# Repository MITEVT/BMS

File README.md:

BMS
===

directory structure
-------------------
software:
firmware:
schematics:

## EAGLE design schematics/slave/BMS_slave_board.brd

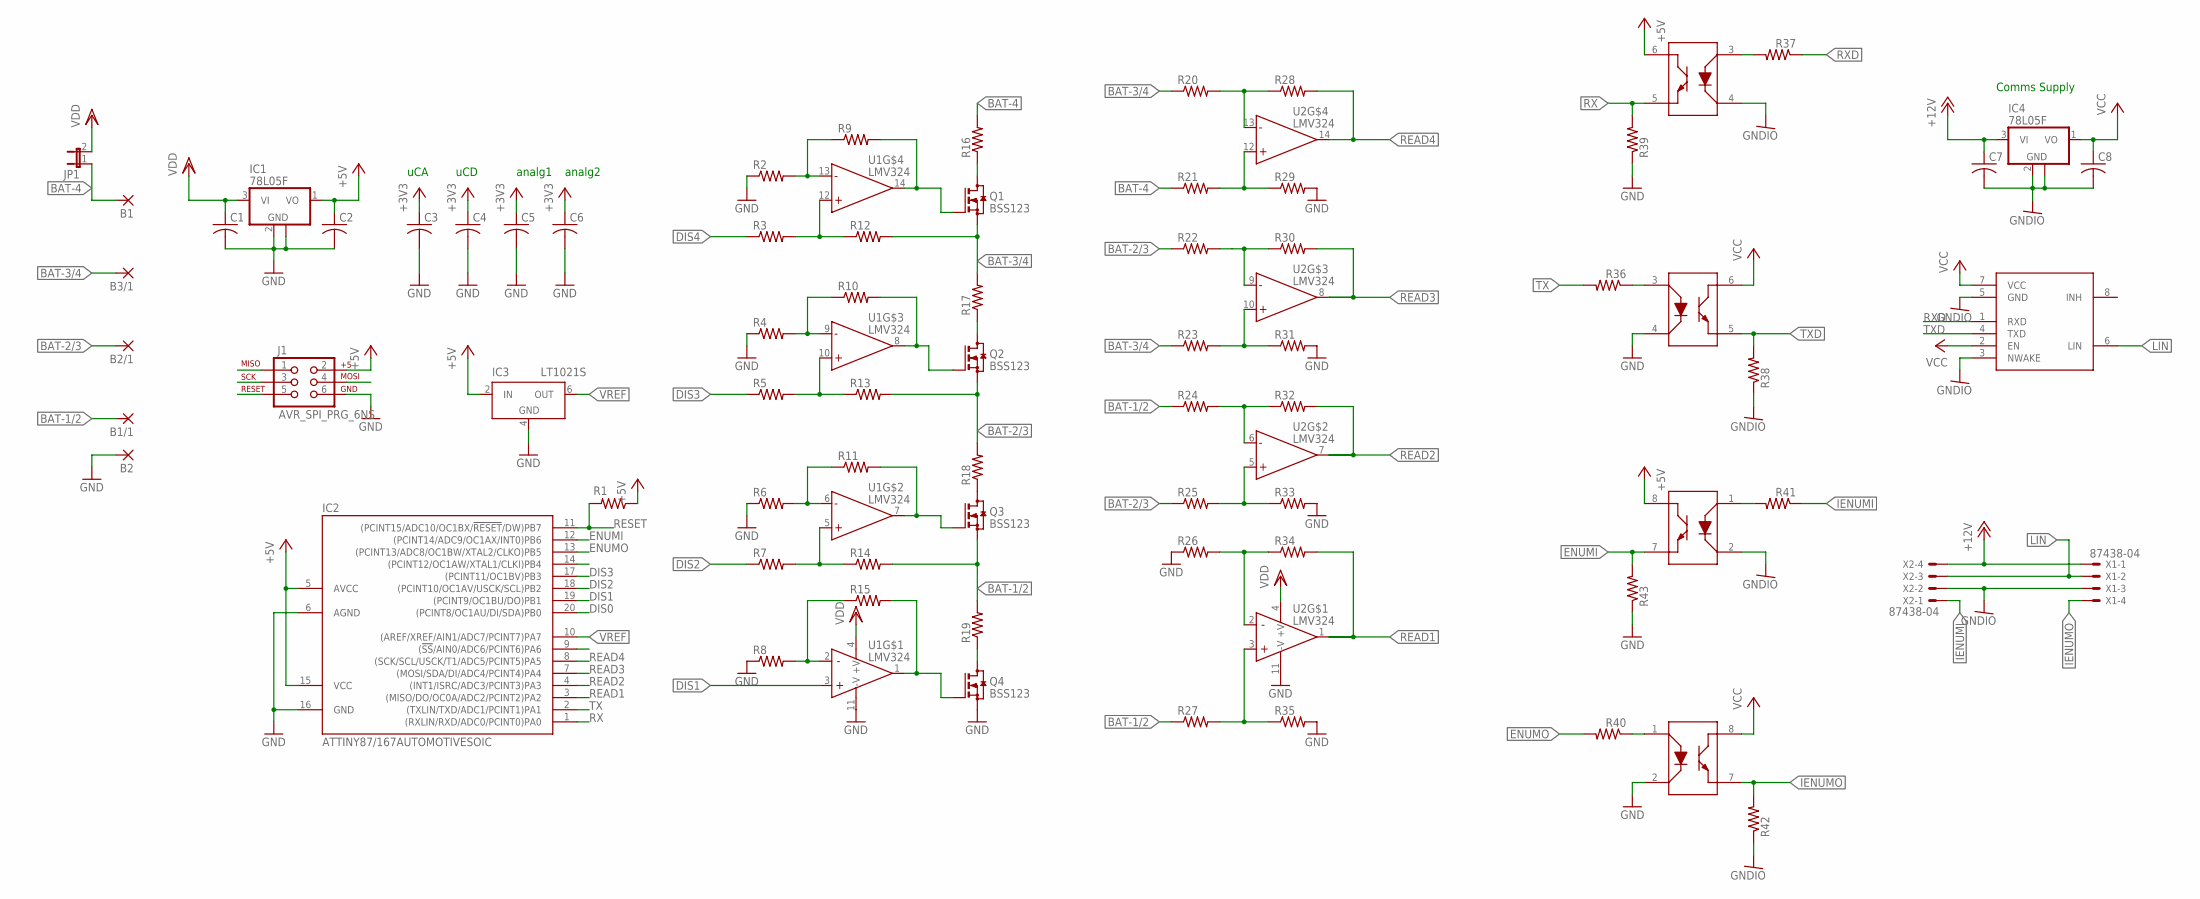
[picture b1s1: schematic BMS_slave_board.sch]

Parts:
B1, B1/1, B2, B2/1, B3/1: 2,15/1,0
C1, C2, C3, C4, C5, C6, C7, C8: C-US025-024X044; C025-024X044
IC1, IC4: 78L05F; SOT89
IC2: ATTINY87/167AUTOMOTIVESOIC; SO20L
IC3: LT1021S; SOIC8
J1: AVR_SPI_PRG_6NS; 2X3-NS
JP1: JP1E; JP1
Q1, Q2, Q3, Q4: BSS123; SOT23
R1, R2, R3, R4, R5, R6, R7, R8, R9, R10, R11, R12, R13, R14, R15, R16, R17, R18, R19, R21, R22, R23, R24, R25, R26, R27, R28, R29, R30, R31, R32, R33, R34, R35, R36, R37, R38, R39, R40, R41, R42, R43: R-US_R0603; R0603
R20: R-US_M0805; M0805
U1, U2: LMV324; SO014
U$1, U$2: LTV-827SMD; SO08
U$3: TPIC1021; SO08
X1, X2: 87438-04

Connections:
+3V3: C3.1, C4.1, C5.1, C6.1
+5V: C2.1, IC1.1 (VO), IC2.5 (AVCC), IC2.15 (VCC), IC3.2 (IN), J1.2, R1.1, U$2.6 (CO), U$2.8 (CO)
+12V: C7.1, IC4.3 (VI), X1.1, X2.4
BAT-1/2: B1/1.1, Q3.2 (S), R14.2, R19.2, R24.1, R27.1
BAT-2/3: B2/1.1, Q2.2 (S), R13.2, R18.2, R22.1, R25.1
BAT-3/4: B3/1.1, Q1.2 (S), R12.2, R17.2, R20.1, R23.1
BAT-4: B1.1, JP1.1, R16.2, R21.1
DELDEL: R4.2, R10.1, U1.9 (-IN)
DIS0: IC2.20 ((PCINT8/OC1AU/DI/SDA)PB0)
DIS1: IC2.19 ((PCINT9/OC1BU/DO)PB1), U1.3 (+IN)
DIS2: IC2.18 ((PCINT10/OC1AV/USCK/SCL)PB2), R7.1
DIS3: IC2.17 ((PCINT11/OC1BV)PB3), R5.1
DIS4: R3.1
ENUMI: IC2.12 ((PCINT14/ADC9/OC1AX/INT0)PB6), R43.2, U$2.7 (E)
ENUMO: IC2.13 ((PCINT13/ADC8/OC1BW/XTAL2/CLKO)PB5), R40.2
GNDIO: C7.2, C8.2, IC4.2 (GND), IC4.2@1 (GND), R38.1, R42.1, U$2.2 (CA), U$2.4 (CA), U$3.3 (NWAKE), U$3.5 (GND), X1.3, X2.2
IENUMI: R41.1, X2.1
IENUMO: R42.2, U$1.7 (E), X1.4
IOGND: B2.1, C1.2, C2.2, C3.2, C4.2, C5.2, C6.2, IC1.2 (GND), IC1.2@1 (GND), IC2.6 (AGND), IC2.16 (GND), IC3.4 (GND), J1.6, Q4.2 (S), R2.1, R4.1, R6.1, R8.1, R26.1, R29.2, R31.2, R33.2, R35.2, R39.1, R43.1, U1.11 (-V), U2.11 (-V), U$1.2 (CA), U$1.4 (CA)
LIN: U$3.6 (LIN), X1.2, X2.3
unnamed: Q2.3 (D), R17.1
unnamed: R5.2, R13.1, U1.10 (+IN)
unnamed: Q3.3 (D), R18.1
unnamed: R8.2, R15.1, U1.2 (-IN)
unnamed: Q1.3 (D), R16.1
unnamed: Q3.1 (G), R11.2, U1.7 (OUT)
unnamed: Q4.3 (D), R19.1
unnamed: Q4.1 (G), R15.2, U1.1 (OUT)
unnamed: Q2.1 (G), R10.2, U1.8 (OUT)
unnamed: R7.2, R14.1, U1.5 (+IN)
unnamed: R20.2, R28.1, U2.13 (-IN)
unnamed: R6.2, R11.1, U1.6 (-IN)
unnamed: R22.2, R30.1, U2.9 (-IN)
unnamed: R2.2, R9.1, U1.13 (-IN)
unnamed: R3.2, R12.1, U1.12 (+IN)
unnamed: R21.2, R29.1, U2.12 (+IN)
unnamed: R23.2, R31.1, U2.10 (+IN)
unnamed: R25.2, R33.1, U2.5 (+IN)
unnamed: R27.2, R35.1, U2.3 (+IN)
unnamed: R24.2, R32.1, U2.6 (-IN)
unnamed: R26.2, R34.1, U2.2 (-IN)
unnamed: R41.2, U$2.1 (A)
unnamed: R40.1, U$1.1 (A)
unnamed: R36.1, U$1.3 (A)
unnamed: R37.2, U$2.3 (A)
unnamed: Q1.1 (G), R9.2, U1.14 (OUT)
READ1: IC2.3 ((MISO/DO/OC0A/ADC2/PCINT2)PA2), J1.1, R34.2, U2.1 (OUT)
READ2: IC2.4 ((INT1/ISRC/ADC3/PCINT3)PA3), R32.2, U2.7 (OUT)
READ3: IC2.7 ((MOSI/SDA/DI/ADC4/PCINT4)PA4), J1.4, R30.2, U2.8 (OUT)
READ4: IC2.8 ((SCK/SCL/USCK/T1/ADC5/PCINT5)PA5), J1.3, R28.2, U2.14 (OUT)
RESET: IC2.11 ((PCINT15/ADC10/OC1BX/!RESET!/DW)PB7), J1.5, R1.2
RX: IC2.1 ((RXLIN/RXD/ADC0/PCINT0)PA0), R39.2, U$2.5 (E)
RXD: R37.1, U$3.1 (RXD)
TX: IC2.2 ((TXLIN/TXD/ADC1/PCINT1)PA1), R36.2
TXD: R38.2, U$1.5 (E), U$3.4 (TXD)
VCC: C8.1, IC4.1 (VO), U$1.6 (CO), U$1.8 (CO), U$3.2 (EN), U$3.7 (VCC)
VDD: C1.1, IC1.3 (VI), JP1.2, U1.4 (+V), U2.4 (+V)
VREF: IC2.10 ((AREF/XREF/AIN1/ADC7/PCINT7)PA7), IC3.6 (OUT)

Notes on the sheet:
uCA
uCD
analg1
analg2
Comms Supply

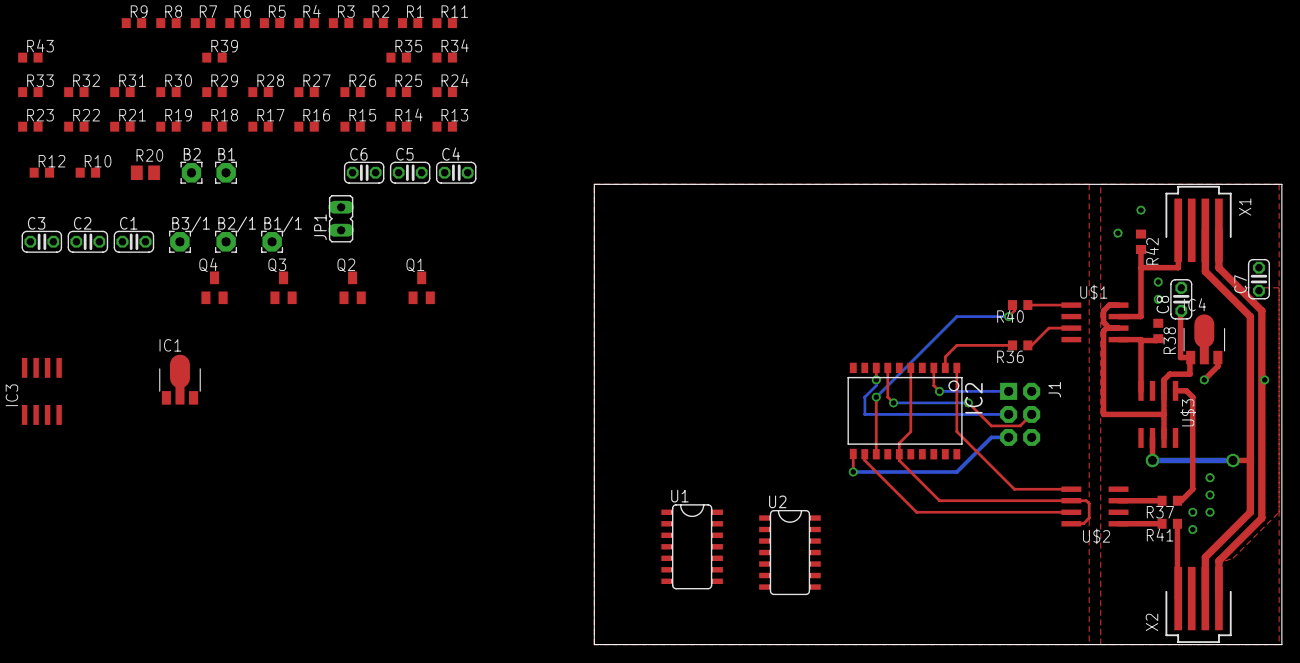
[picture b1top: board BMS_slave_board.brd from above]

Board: 2 copper layers, 75.9 x 50.8 mm, 73 parts (0 on the bottom side), 56 nets.

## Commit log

2013-10-26 innitial schematic commit
2013-10-26 edited readme
2013-10-26 Created folders for master and slave schematics.
2013-10-26 changed schematic directory structure
2013-10-26 added component selection file
2013-10-26 trying to fix some stuff
2013-10-26 Added microcontroller to bill of materials
2013-10-26 added master component selection doc
2013-10-27 worked on the slave BMS schematic
2013-10-28 added .gitignore
2013-10-28 selected new microcontroller for slave
2013-10-30 Added microcontroller and cleanded analog work
    Added the Attiny261, ISP header, linear regulator (and associated
    discretes)
2013-10-31 added voltage regulator and new uC symbol
    also added decoupling caps for analog power supply and cleaned up wiring
2013-11-02 added optoisolators and Master supply for optos
    optos belong on slave to prevent a wide variety of voltages on master
    but may be moved for space considerations. If we move 'em we have to
    feed ground and power from each slave to the master.
2013-11-02 added mux and demux to master for slaves
2013-11-09 added maste supply
2013-11-09 modified power supplies
2013-11-09 innitial layout
2013-11-16 deleted old opto's and added attiny87
2013-11-19 added new optos, moved around pins as necessary and added LIN Driver
2013-11-20 Re-connected sense outputs to analog ins of chip.
    Added a power jumber to turn off the 5vReg and the Opamps to allow for programming
2013-11-20 added dual optos for automatic linear enumeration
    added header for the daisy chaining of the bus
2013-11-22 playing with intterupt vectors and firware and junk
2013-11-24 added avr LIN driver and implimented our custom higher level protocol
2013-11-27 random bugfixes and moving around the output enable line
2013-11-28 added innitial board. routed isolated LIN set dimensions
    modified schematic to make certain pins more convenient
2013-11-30 worked on ground plane and power pour
2013-12-01 more work on the ground plane
2013-12-20 added innitial simulator files
2013-12-24 added general tollerance function removed pyc

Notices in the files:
parts and their libraries:
SparkFun-AnalogIC: Licensing: CC v3.0 Share-Alike You are welcome to use this library for commercial purposes.
